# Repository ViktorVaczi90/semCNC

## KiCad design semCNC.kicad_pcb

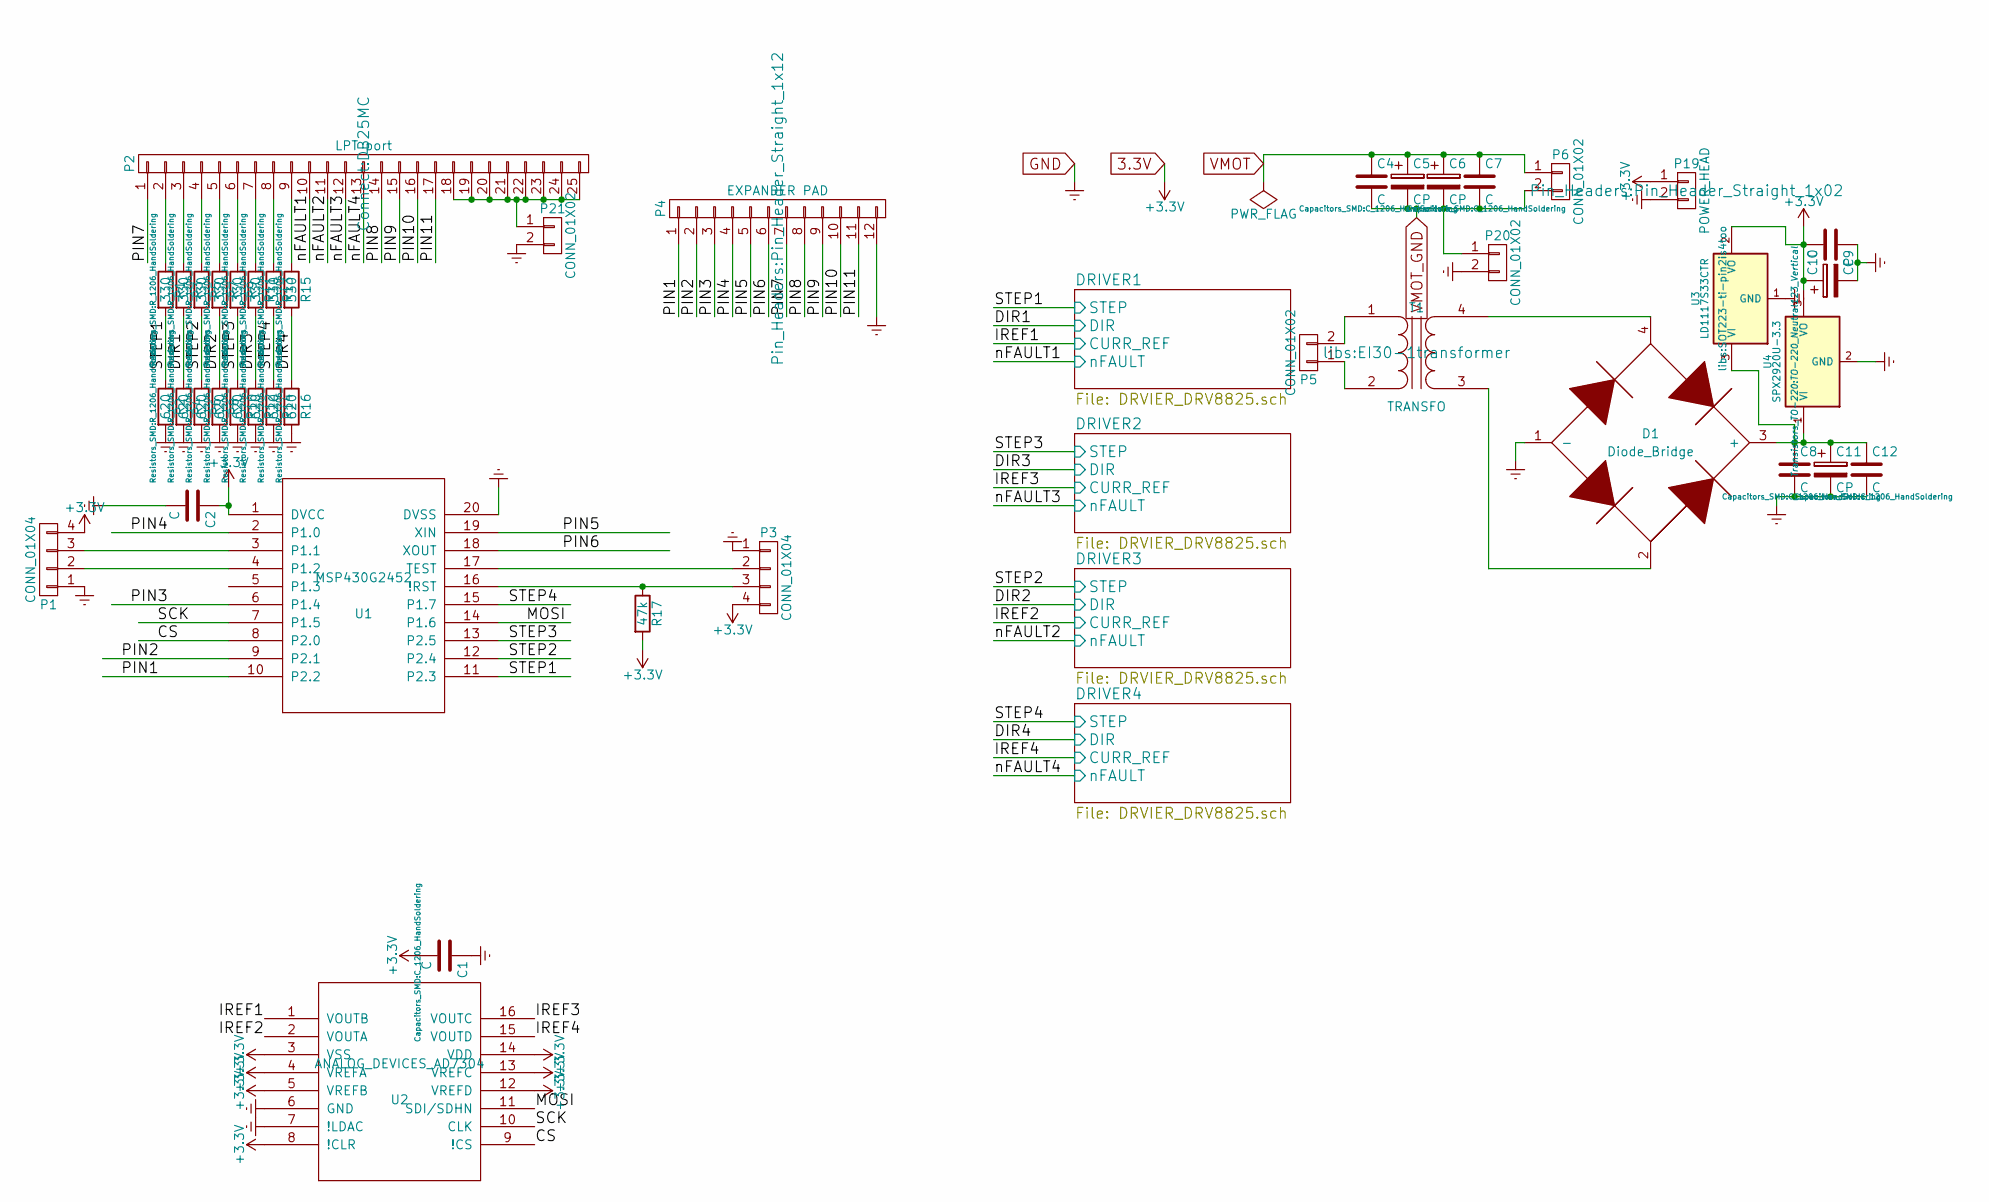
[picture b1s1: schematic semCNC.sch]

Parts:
C1, C2, C4, C7, C8, C9, C12: C; C_1206_HandSoldering
C5, C6: CP; MultiPolCAP_3.5_5_7.5_10
C10, C11: CP; C_Radial_D8_L11.5_P3.5
D1: Diode_Bridge; rb1a_mb6sbridge
P1, P3: CONN_01X04; Pin_Header_Straight_1x04
P2: LPT port; DB25MC
P4: EXPANDER PAD; Pin_Header_Straight_1x12
P5, P6: CONN_01X02; PIN_CONN_0.3Inch
P19: POWER_HEAD; Pin_Header_Straight_1x02
P20, P21: CONN_01X02; Pin_Header_Straight_1x02
R1, R3, R5, R7, R9, R11, R13, R15: 330; R_1206_HandSoldering
R2, R4, R6, R8, R10, R12, R14, R16: 620; R_1206_HandSoldering
R17: 47k; R_1206_HandSoldering
T1: TRANSFO; EI30-1transformer
U1: MSP430G2452; msp430g2452
U2: ANALOG_DEVICES_AD7304; SOIC-16_7.5x10.3mm_Pitch1.27mm
U3: LD1117S33CTR; SOT223-ti-pin2is4too
U4: SPX2920U-3.3; TO-220_Neutral123_Vertical

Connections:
3.3V: C1.2, C2.1, C9.2, C10.1, P1.4, P3.4, P19.1, R17.2, U1.1 (DVCC), U2.3 (VSS), U2.4 (VREFA), U2.5 (VREFB), U2.8 (!CLR), U2.12 (VREFD), U2.13 (VREFC), U2.14 (VDD), U3.2 (VO), U4.3 (VO); also elsewhere on the board
/CS: U1.8 (P2.0), U2.9 (!CS)
/DRIVER1/CURR_REF: U2.1 (VOUTB); also elsewhere on the board
/DRIVER1/DIR: R3.2, R4.1; also elsewhere on the board
/DRIVER1/STEP: R1.2, R2.1, U1.11 (P2.3); also elsewhere on the board
/DRIVER1/nFAULT: P2.10; also elsewhere on the board
/DRIVER2/CURR_REF: U2.16 (VOUTC); also elsewhere on the board
/DRIVER2/DIR: R11.2, R12.1; also elsewhere on the board
/DRIVER2/STEP: R9.2, R10.1, U1.13 (P2.5); also elsewhere on the board
/DRIVER2/nFAULT: P2.12; also elsewhere on the board
/DRIVER3/CURR_REF: U2.2 (VOUTA); also elsewhere on the board
/DRIVER3/DIR: R7.2, R8.1; also elsewhere on the board
/DRIVER3/STEP: R5.2, R6.1, U1.12 (P2.4); also elsewhere on the board
/DRIVER3/nFAULT: P2.11; also elsewhere on the board
/DRIVER4/CURR_REF: U2.15 (VOUTD); also elsewhere on the board
/DRIVER4/DIR: R15.2, R16.1; also elsewhere on the board
/DRIVER4/STEP: R13.2, R14.1, U1.15 (P1.7); also elsewhere on the board
/DRIVER4/nFAULT: P2.13; also elsewhere on the board
/MOSI: U1.14 (P1.6), U2.11 (SDI/SDHN)
/PIN1: P4.1, U1.10 (P2.2)
/PIN2: P4.2, U1.9 (P2.1)
/PIN3: P4.3, U1.6 (P1.4)
/PIN4: P4.4, U1.2 (P1.0)
/PIN5: P4.5, U1.19 (XIN)
/PIN6: P4.6, U1.18 (XOUT)
/PIN7: P2.1, P4.7
/PIN8: P2.14, P4.8
/PIN9: P2.15, P4.9
/PIN10: P2.16, P4.10
/PIN11: P2.17, P4.11
/SCK: U1.7 (P1.5), U2.10 (CLK)
GND: C1.1, C2.2, C8.2, C9.1, C10.2, C11.2, C12.2, D1.1 (-), P1.1, P3.1, P4.12, P19.2, P20.2, P21.2, R2.2, R4.2, R6.2, R8.2, R10.2, R12.2, R14.2, R16.2, U1.20 (DVSS), U2.6 (GND), U2.7 (!LDAC), U3.1 (GND), U4.2 (GND); also elsewhere on the board
unnamed: C8.1, C11.1, C12.1, D1.3 (+), U3.3 (VI), U4.1 (VI)
unnamed: D1.2, T1.3 (SA)
unnamed: D1.4, T1.4 (SB)
unnamed: P1.2, U1.4 (P1.2)
unnamed: P1.3, U1.3 (P1.1)
unnamed: P2.2, R1.1
unnamed: P2.3, R3.1
unnamed: P2.4, R5.1
unnamed: P2.5, R7.1
unnamed: P2.6, R9.1
unnamed: P2.7, R11.1
unnamed: P2.8, R13.1
unnamed: P2.9, R15.1
unnamed: P2.18, P2.19, P2.20, P2.21, P2.22, P2.23, P2.24, P2.25, P21.1
unnamed: P3.2, U1.17 (TEST)
unnamed: P3.3, R17.1, U1.16 (!RST)
unnamed: P5.1, T1.2 (AB)
unnamed: P5.2, T1.1 (AA)
VMOT: C4.1, C5.1, C6.1, C7.1, P6.1; also elsewhere on the board
VMOT_GND: C4.2, C5.2, C6.2, C7.2, P6.2, P20.1; also elsewhere on the board

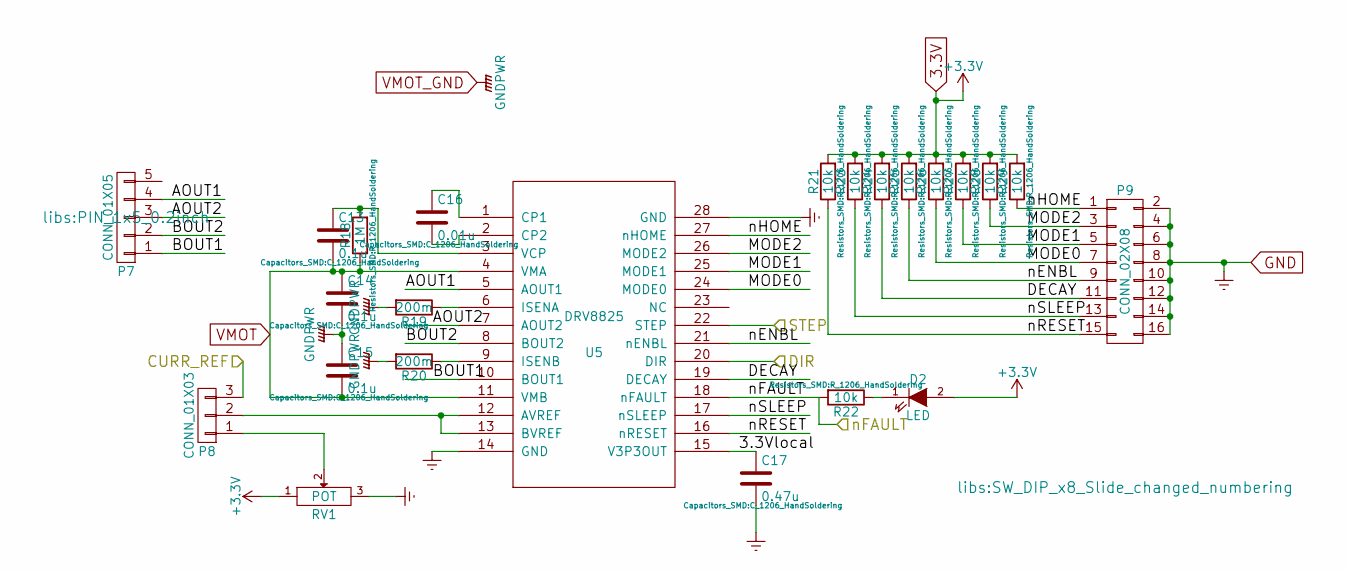
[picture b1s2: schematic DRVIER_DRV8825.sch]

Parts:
C13, C14, C15: 0.1u; C_1206_HandSoldering
C16: 0.01u; C_1206_HandSoldering
C17: 0.47u; C_1206_HandSoldering
D2: LED; LED-5MM
P7: CONN_01X05; PIN_1x5_0.2inch
P8: CONN_01X03; Pin_Header_Straight_1x03
P9: CONN_02X08; SW_DIP_x8_Slide_changed_numbering
R18: 1M; R_1206_HandSoldering
R19, R20: 200m; Resistor_Horizontal_RM15mm
R21, R22, R23, R24, R25, R26, R27, R28, R29: 10k; R_1206_HandSoldering
RV1: POT; Potentiometer_Bourns_3296P_3-8Zoll_Angular_ScrewFront
U5: DRV8825; drv8825

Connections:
3.3V: D2.2 (A), R21.2, R23.2, R24.2, R25.2, R26.2, R27.2, R28.2, R29.2, RV1.1; also elsewhere on the board
/DRIVER1/3.3Vlocal: C17.1, U5.15 (V3P3OUT)
/DRIVER1/AOUT1: P7.4, U5.5 (AOUT1)
/DRIVER1/AOUT2: P7.3, U5.7 (AOUT2)
/DRIVER1/BOUT1: P7.1, U5.10 (BOUT1)
/DRIVER1/BOUT2: P7.2, U5.8 (BOUT2)
/DRIVER1/CURR_REF: P8.3; also elsewhere on the board
/DRIVER1/DECAY: P9.11, R24.1, U5.19 (DECAY)
/DRIVER1/DIR: U5.20 (DIR); also elsewhere on the board
/DRIVER1/MODE0: P9.7, R26.1, U5.24 (MODE0)
/DRIVER1/MODE1: P9.5, R27.1, U5.25 (MODE1)
/DRIVER1/MODE2: P9.3, R28.1, U5.26 (MODE2)
/DRIVER1/STEP: U5.22 (STEP); also elsewhere on the board
/DRIVER1/nENBL: P9.9, R25.1, U5.21 (nENBL)
/DRIVER1/nFAULT: R22.2, U5.18 (nFAULT); also elsewhere on the board
/DRIVER1/nHOME: P9.1, R29.1, U5.27 (nHOME)
/DRIVER1/nRESET: P9.15, R21.1, U5.16 (nRESET)
/DRIVER1/nSLEEP: P9.13, R23.1, U5.17 (nSLEEP)
GND: C17.2, P9.2, P9.4, P9.6, P9.8, P9.10, P9.12, P9.14, P9.16, RV1.3, U5.14 (GND), U5.28 (GND); also elsewhere on the board
unnamed: C13.1, R18.2, U5.3 (VCP)
unnamed: C16.1, U5.1 (CP1)
unnamed: C16.2, U5.2 (CP2)
unnamed: D2.1 (K), R22.1
unnamed: P8.1, RV1.2
unnamed: P8.2, U5.12 (AVREF), U5.13 (BVREF)
unnamed: R19.1, U5.6 (ISENA)
unnamed: R20.1, U5.9 (ISENB)
VMOT: C13.2, C14.1, C15.2, R18.1, U5.4 (VMA), U5.11 (VMB); also elsewhere on the board
VMOT_GND: C14.2, C15.1, R19.2, R20.2; also elsewhere on the board

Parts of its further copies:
C18, C19, C20, C23, C24, C25, C28, C29, C30: 0.1u; C_1206_HandSoldering
C21, C26, C31: 0.01u; C_1206_HandSoldering
C22, C27, C32: 0.47u; C_1206_HandSoldering
D3, D4, D5: LED; LED-5MM
P10, P13, P16: CONN_01X05; PIN_1x5_0.2inch
P11, P14, P17: CONN_01X03; Pin_Header_Straight_1x03
P12, P15, P18: CONN_02X08; SW_DIP_x8_Slide_changed_numbering
R30, R42, R54: 1M; R_1206_HandSoldering
R31, R32, R43, R44, R55, R56: 200m; Resistor_Horizontal_RM15mm
R33, R34, R35, R36, R37, R38, R39, R40, R41, R45, R46, R47, R48, R49, R50, R51, R52, R53, R57, R58, R59, R60, R61, R62, R63, R64, R65: 10k; R_1206_HandSoldering
RV2, RV3, RV4: POT; Potentiometer_Bourns_3296P_3-8Zoll_Angular_ScrewFront
U6, U7, U8: DRV8825; drv8825

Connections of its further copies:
3.3V: D3.2 (A), D4.2 (A), D5.2 (A), R33.2, R35.2, R36.2, R37.2, R38.2, R39.2, R40.2, R41.2, R45.2, R47.2, R48.2, R49.2, R50.2, R51.2, R52.2, R53.2, R57.2, R59.2, R60.2, R61.2, R62.2, R63.2, R64.2, R65.2, RV2.1, RV3.1, RV4.1; also elsewhere on the board
/DRIVER2/3.3Vlocal: C22.1, U6.15 (V3P3OUT)
/DRIVER2/AOUT1: P10.4, U6.5 (AOUT1)
/DRIVER2/AOUT2: P10.3, U6.7 (AOUT2)
/DRIVER2/BOUT1: P10.1, U6.10 (BOUT1)
/DRIVER2/BOUT2: P10.2, U6.8 (BOUT2)
/DRIVER2/CURR_REF: P11.3; also elsewhere on the board
/DRIVER2/DECAY: P12.11, R36.1, U6.19 (DECAY)
/DRIVER2/DIR: U6.20 (DIR); also elsewhere on the board
/DRIVER2/MODE0: P12.7, R38.1, U6.24 (MODE0)
/DRIVER2/MODE1: P12.5, R39.1, U6.25 (MODE1)
/DRIVER2/MODE2: P12.3, R40.1, U6.26 (MODE2)
/DRIVER2/STEP: U6.22 (STEP); also elsewhere on the board
/DRIVER2/nENBL: P12.9, R37.1, U6.21 (nENBL)
/DRIVER2/nFAULT: R34.2, U6.18 (nFAULT); also elsewhere on the board
/DRIVER2/nHOME: P12.1, R41.1, U6.27 (nHOME)
/DRIVER2/nRESET: P12.15, R33.1, U6.16 (nRESET)
/DRIVER2/nSLEEP: P12.13, R35.1, U6.17 (nSLEEP)
/DRIVER3/3.3Vlocal: C27.1, U7.15 (V3P3OUT)
/DRIVER3/AOUT1: P13.4, U7.5 (AOUT1)
/DRIVER3/AOUT2: P13.3, U7.7 (AOUT2)
/DRIVER3/BOUT1: P13.1, U7.10 (BOUT1)
/DRIVER3/BOUT2: P13.2, U7.8 (BOUT2)
/DRIVER3/CURR_REF: P14.3; also elsewhere on the board
/DRIVER3/DECAY: P15.11, R48.1, U7.19 (DECAY)
/DRIVER3/DIR: U7.20 (DIR); also elsewhere on the board
/DRIVER3/MODE0: P15.7, R50.1, U7.24 (MODE0)
/DRIVER3/MODE1: P15.5, R51.1, U7.25 (MODE1)
/DRIVER3/MODE2: P15.3, R52.1, U7.26 (MODE2)
/DRIVER3/STEP: U7.22 (STEP); also elsewhere on the board
/DRIVER3/nENBL: P15.9, R49.1, U7.21 (nENBL)
/DRIVER3/nFAULT: R46.2, U7.18 (nFAULT); also elsewhere on the board
/DRIVER3/nHOME: P15.1, R53.1, U7.27 (nHOME)
/DRIVER3/nRESET: P15.15, R45.1, U7.16 (nRESET)
/DRIVER3/nSLEEP: P15.13, R47.1, U7.17 (nSLEEP)
/DRIVER4/3.3Vlocal: C32.1, U8.15 (V3P3OUT)
/DRIVER4/AOUT1: P16.4, U8.5 (AOUT1)
/DRIVER4/AOUT2: P16.3, U8.7 (AOUT2)
/DRIVER4/BOUT1: P16.1, U8.10 (BOUT1)
/DRIVER4/BOUT2: P16.2, U8.8 (BOUT2)
/DRIVER4/CURR_REF: P17.3; also elsewhere on the board
/DRIVER4/DECAY: P18.11, R60.1, U8.19 (DECAY)
/DRIVER4/DIR: U8.20 (DIR); also elsewhere on the board
/DRIVER4/MODE0: P18.7, R62.1, U8.24 (MODE0)
/DRIVER4/MODE1: P18.5, R63.1, U8.25 (MODE1)
/DRIVER4/MODE2: P18.3, R64.1, U8.26 (MODE2)
/DRIVER4/STEP: U8.22 (STEP); also elsewhere on the board
/DRIVER4/nENBL: P18.9, R61.1, U8.21 (nENBL)
/DRIVER4/nFAULT: R58.2, U8.18 (nFAULT); also elsewhere on the board
/DRIVER4/nHOME: P18.1, R65.1, U8.27 (nHOME)
/DRIVER4/nRESET: P18.15, R57.1, U8.16 (nRESET)
/DRIVER4/nSLEEP: P18.13, R59.1, U8.17 (nSLEEP)
GND: C22.2, C27.2, C32.2, P12.2, P12.4, P12.6, P12.8, P12.10, P12.12, P12.14, P12.16, P15.2, P15.4, P15.6, P15.8, P15.10, P15.12, P15.14, P15.16, P18.2, P18.4, P18.6, P18.8, P18.10, P18.12, P18.14, P18.16, RV2.3, RV3.3, RV4.3, U6.14 (GND), U6.28 (GND), U7.14 (GND), U7.28 (GND), U8.14 (GND), U8.28 (GND); also elsewhere on the board
unnamed: C18.1, R30.2, U6.3 (VCP)
unnamed: C21.1, U6.1 (CP1)
unnamed: C21.2, U6.2 (CP2)
unnamed: C23.1, R42.2, U7.3 (VCP)
unnamed: C26.1, U7.1 (CP1)
unnamed: C26.2, U7.2 (CP2)
unnamed: C28.1, R54.2, U8.3 (VCP)
unnamed: C31.1, U8.1 (CP1)
unnamed: C31.2, U8.2 (CP2)
unnamed: D3.1 (K), R34.1
unnamed: D4.1 (K), R46.1
unnamed: D5.1 (K), R58.1
unnamed: P11.1, RV2.2
unnamed: P11.2, U6.12 (AVREF), U6.13 (BVREF)
unnamed: P14.1, RV3.2
unnamed: P14.2, U7.12 (AVREF), U7.13 (BVREF)
unnamed: P17.1, RV4.2
unnamed: P17.2, U8.12 (AVREF), U8.13 (BVREF)
unnamed: R31.1, U6.6 (ISENA)
unnamed: R32.1, U6.9 (ISENB)
unnamed: R43.1, U7.6 (ISENA)
unnamed: R44.1, U7.9 (ISENB)
unnamed: R55.1, U8.6 (ISENA)
unnamed: R56.1, U8.9 (ISENB)
VMOT: C18.2, C19.1, C20.2, C23.2, C24.1, C25.2, C28.2, C29.1, C30.2, R30.1, R42.1, R54.1, U6.4 (VMA), U6.11 (VMB), U7.4 (VMA), U7.11 (VMB), U8.4 (VMA), U8.11 (VMB); also elsewhere on the board
VMOT_GND: C19.2, C20.1, C24.2, C25.1, C29.2, C30.1, R31.2, R32.2, R43.2, R44.2, R55.2, R56.2; also elsewhere on the board

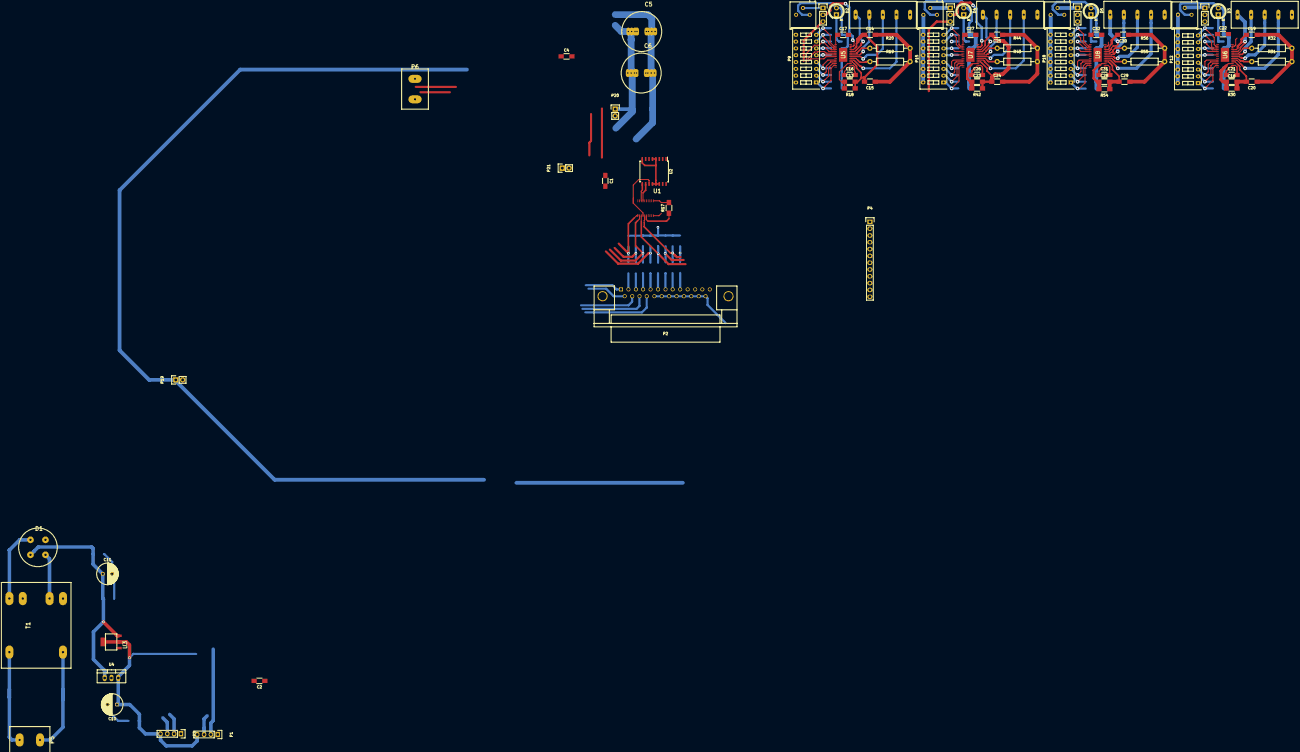
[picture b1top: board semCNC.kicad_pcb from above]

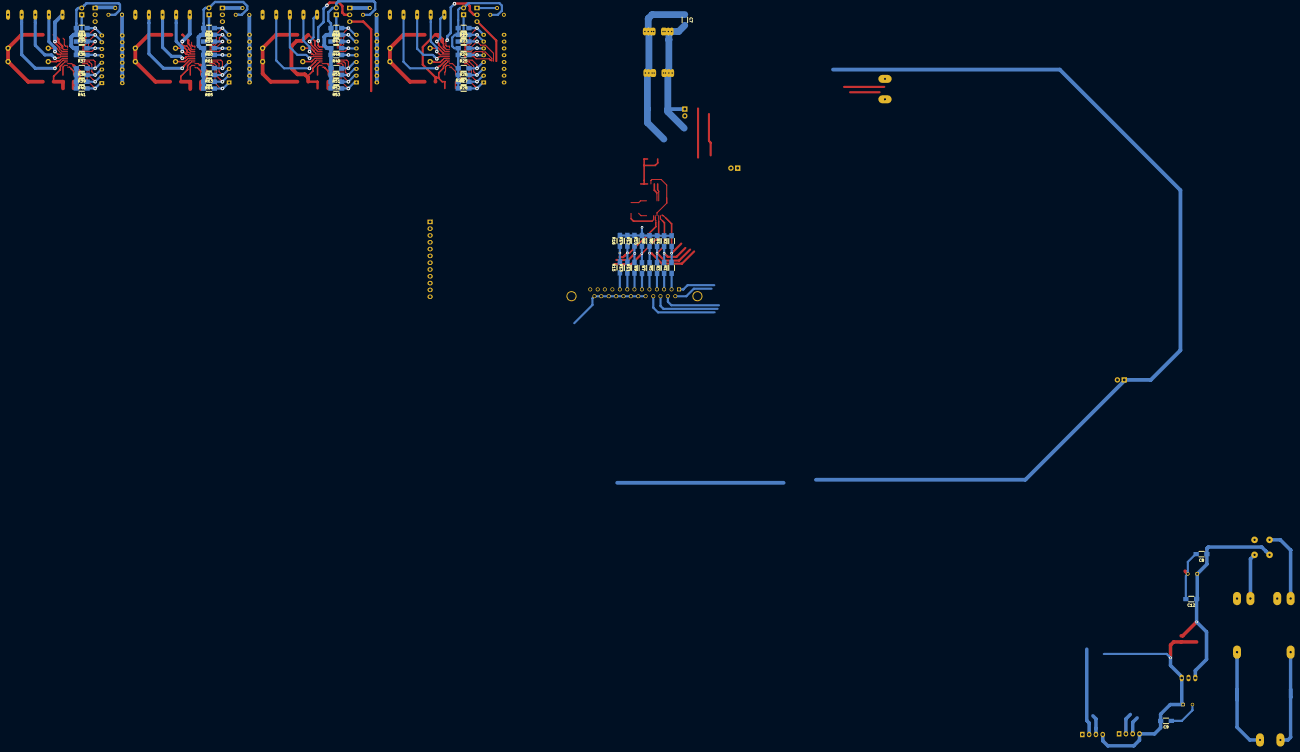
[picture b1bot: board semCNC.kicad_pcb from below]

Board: 2 copper layers, 135 parts (56 on the bottom side), 136 nets.

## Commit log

2015-10-01 some modifications, before creating an array
2015-10-01 Second driver
2015-10-04 new try to commit
2015-10-08 before test
2015-10-08 viktor rendberak mindent
2015-10-08 nyegyedik driver
2015-10-10 4 kesz
2015-10-10 trafo bent
2015-10-10 trafo kesz
2015-10-14 mer elegem van .... :P
2015-10-14 kicsit tovabb
2015-10-19 New layout
2015-11-02 layout work
2016-02-02 minor changes in layout
2016-02-02 layout of drivers ready
